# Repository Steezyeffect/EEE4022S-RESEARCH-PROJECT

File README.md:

# Single-Phase Four-Level Multilevel Inverter - EEE4022S Research Project

This repository hosts the design and development files for a **Single-Phase Four-Level Nested Neutral Point Clamped (NNPC) Multilevel Inverter**. This inverter project focuses on achieving low Total Harmonic Distortion (THD) and enhanced efficiency for renewable energy applications.

## Key Features
- **Four-Level Output**: Improved waveform quality and lower THD.
- **Control Strategy**: PWM control using the TI C2000 microcontroller.
- **Simulation and PCB Design**: Simulink models and KiCAD PCB layouts for testing and prototyping.

Enjoy exploring the project, and thank you for your interest!

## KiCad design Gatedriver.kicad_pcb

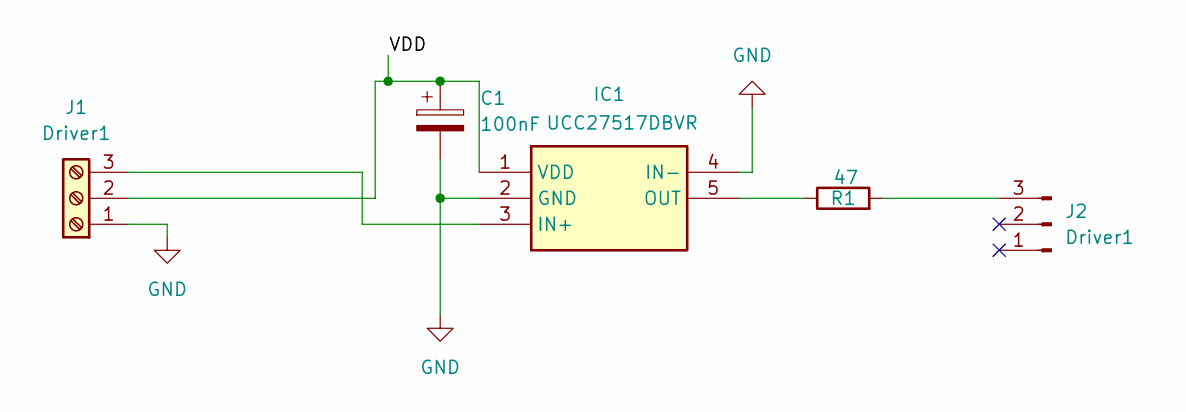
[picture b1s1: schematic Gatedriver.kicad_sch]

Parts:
C1: 100nF; C_Disc_D5.0mm_W2.5mm_P5.00mm
IC1: UCC27517DBVR; SOT-23-5; Manufacturer_Part_Number UCC27517DBVR; Mouser Part Number 595-UCC27517DBVR
J1: Driver1; TerminalBlock_Phoenix_MPT-0,5-3-2.54_1x03_P2.54mm_Horizontal
J2: Driver1; PinHeader_1x03_P2.54mm_Horizontal
R1: 47; R_Axial_DIN0204_L3.6mm_D1.6mm_P5.08mm_Horizontal

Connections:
/VDD: C1.1, IC1.1 (VDD), J1.2
GND: C1.2, IC1.2 (GND), IC1.4 (IN-), J1.1
unnamed: IC1.3 (IN+), J1.3
unnamed: IC1.5 (OUT), R1.1
unnamed: J2.3, R1.2

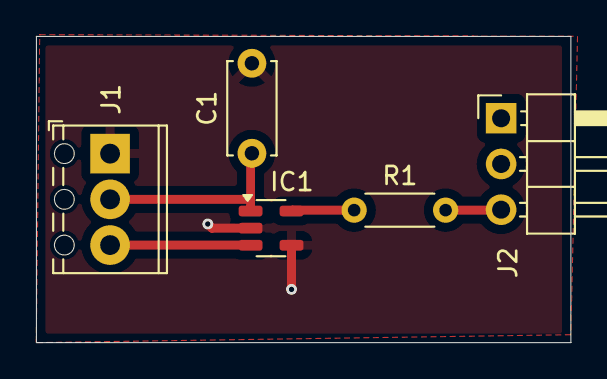
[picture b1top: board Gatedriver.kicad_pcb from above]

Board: 4 copper layers, 29.7 x 17.0 mm, 5 parts (0 on the bottom side), 5 nets.

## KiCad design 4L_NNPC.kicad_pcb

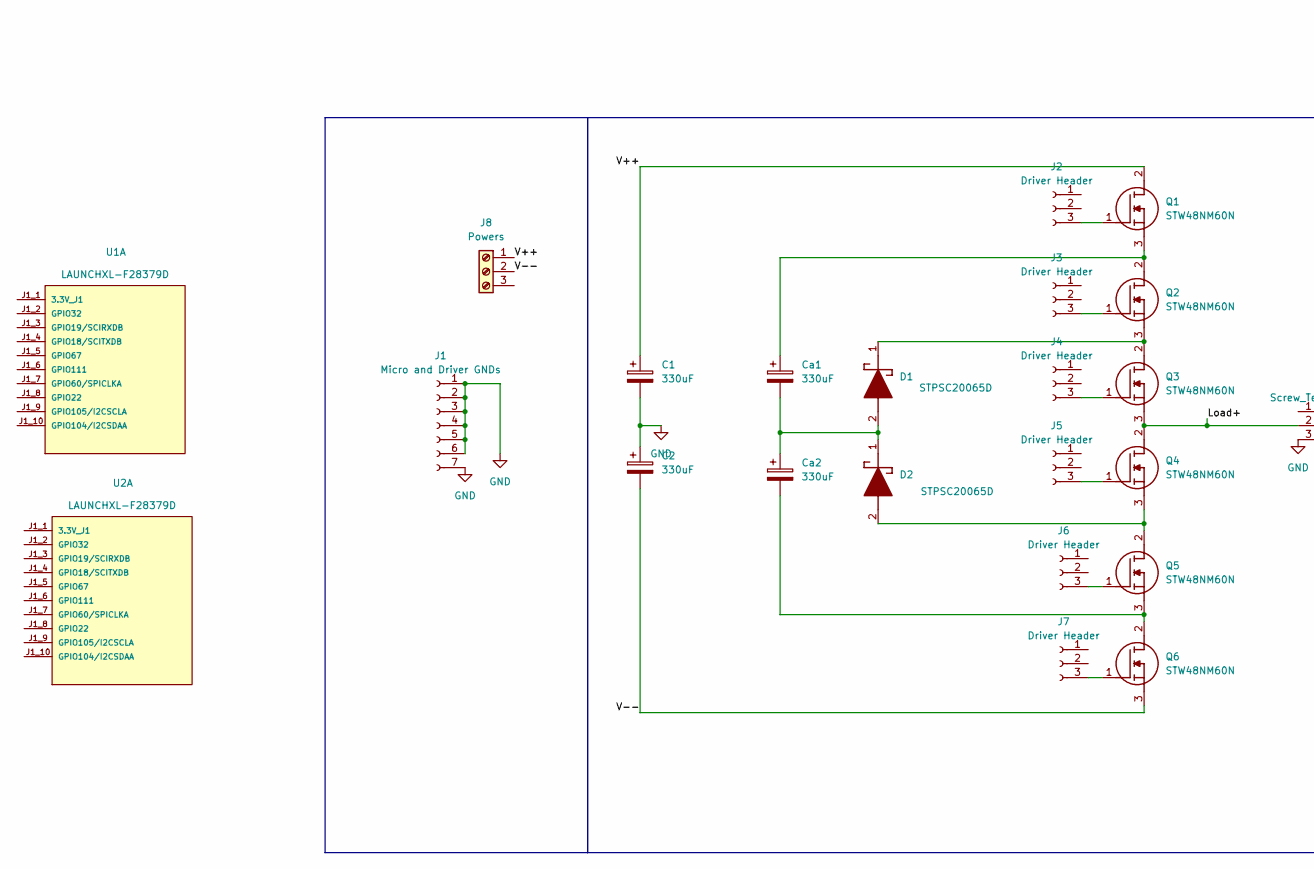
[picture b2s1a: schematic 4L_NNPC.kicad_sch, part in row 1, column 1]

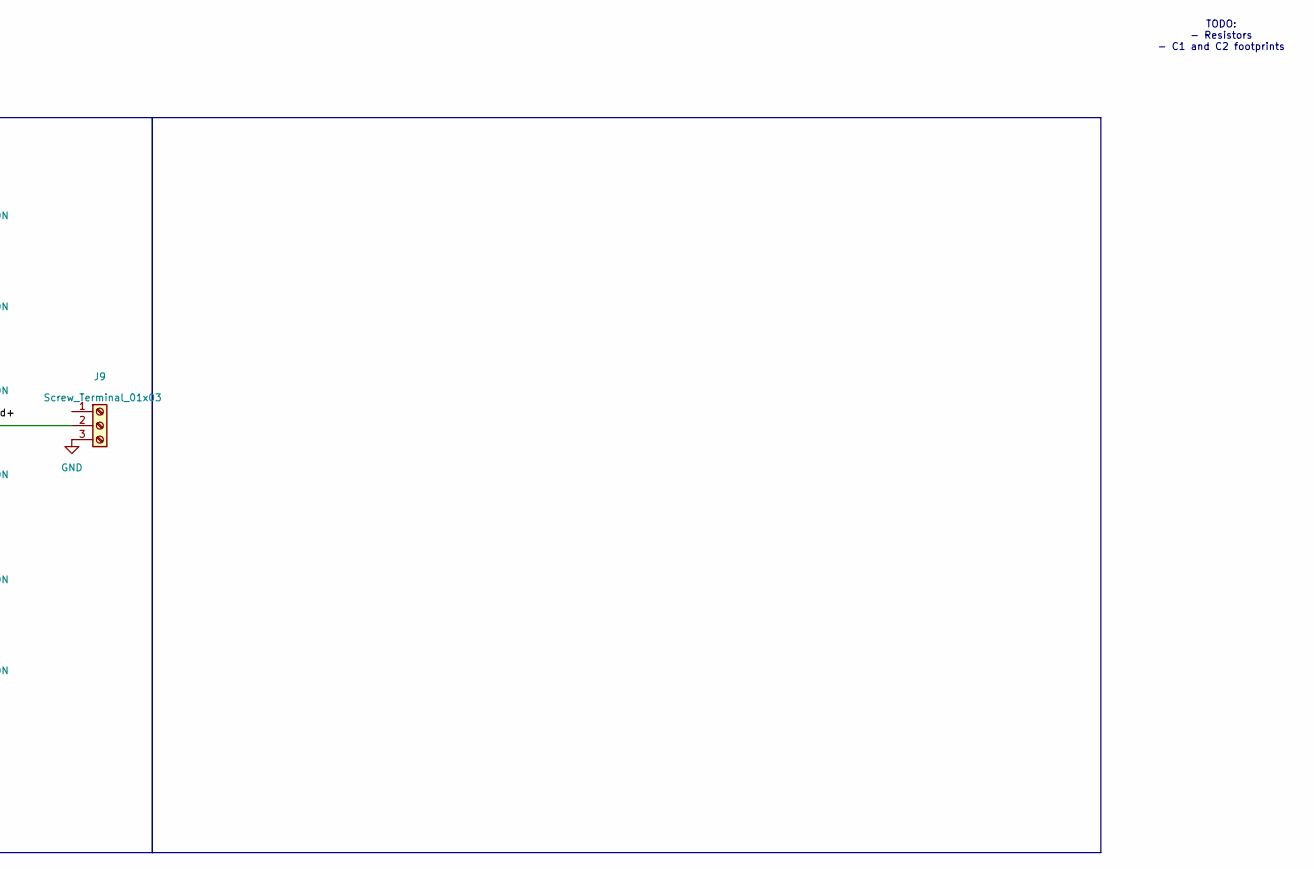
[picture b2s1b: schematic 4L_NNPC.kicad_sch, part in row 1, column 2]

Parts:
C1, C2: 330uF; CP_Radial_D25.0mm_P10.00mm_SnapIn
Ca1, Ca2: 330uF; CP_Radial_D25.0mm_P10.00mm_SnapIn
D1, D2: STPSC20065D; TO-220-2_Vertical; Manufacturer_Part_Number STPSC20065D; Mouser Part Number 511-STPSC20065D
J1: Micro and Driver GNDs; PinSocket_1x07_P2.54mm_Vertical
J2, J3, J4, J5, J6, J7: Driver Header; PinSocket_1x03_P2.54mm_Vertical
J8: Powers; TerminalBlock_Xinya_XY308-2.54-3P_1x03_P2.54mm_Horizontal
J9: Screw_Terminal_01x03; TerminalBlock_Xinya_XY308-2.54-3P_1x03_P2.54mm_Horizontal
Q1, Q2, Q3, Q4, Q5, Q6: STW48NM60N; TO-247-3_Vertical; Manufacturer_Part_Number STW48NM60N; Mouser Part Number 511-STW48NM60N
U1, U2: LAUNCHXL-F28379D; MOD_LAUNCHXL-F28379D; PARTREV 2.0

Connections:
/Load+: J9.2, Q3.3 (S), Q4.2 (D)
/V++: C1.1, J8.1, Q1.2 (D)
/V--: C2.2, J8.2, Q6.3 (S)
GND: C1.2, C2.1, J1.1, J1.2, J1.3, J1.4, J1.5, J1.6, J1.7, J9.3
unnamed: Ca1.2, Ca2.1, D1.2 (A), D2.1 (K)
unnamed: D1.1 (K), Q2.3 (S), Q3.2 (D)
unnamed: D2.2 (A), Q4.3 (S), Q5.2 (D)
unnamed: J2.3, Q1.1 (G)
unnamed: J3.3, Q2.1 (G)
unnamed: J4.3, Q3.1 (G)
unnamed: J5.3, Q4.1 (G)
unnamed: J6.3, Q5.1 (G)
unnamed: J7.3, Q6.1 (G)
unnamed: Ca1.1, Q1.3 (S), Q2.2 (D)
unnamed: Ca2.2, Q5.3 (S), Q6.2 (D)

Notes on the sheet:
TODO: - Resistors - C1 and C2 footprints

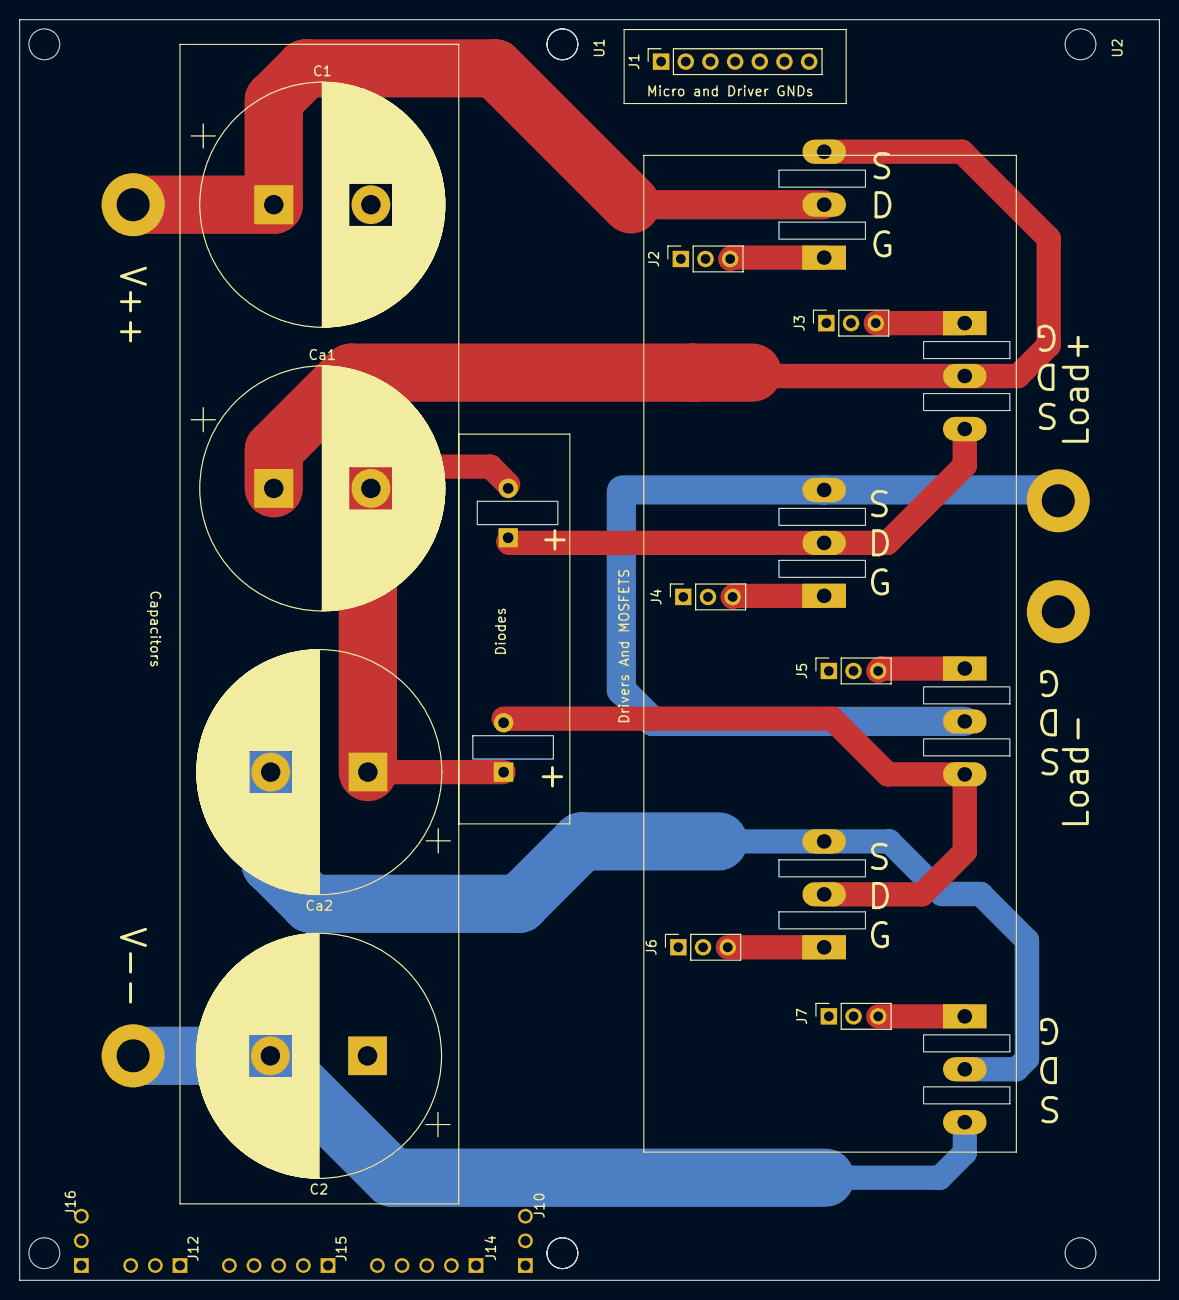
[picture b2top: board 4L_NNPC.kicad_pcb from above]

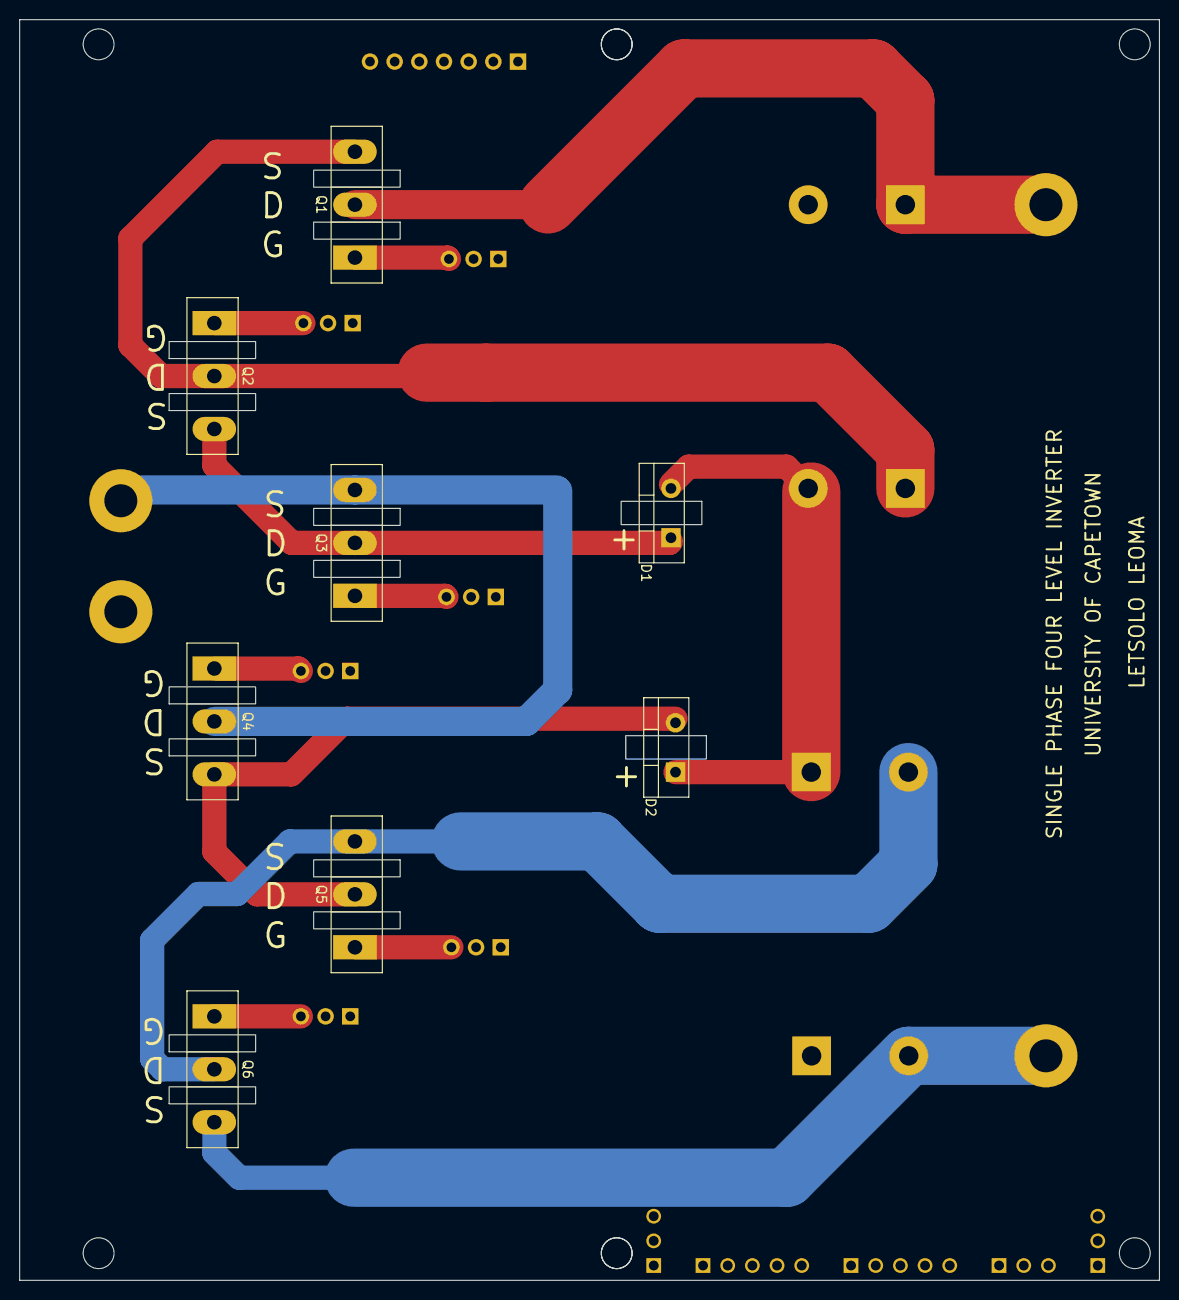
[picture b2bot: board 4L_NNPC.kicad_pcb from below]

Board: 4 copper layers, 117.3 x 129.8 mm, 21 parts (8 on the bottom side), 15 nets.
